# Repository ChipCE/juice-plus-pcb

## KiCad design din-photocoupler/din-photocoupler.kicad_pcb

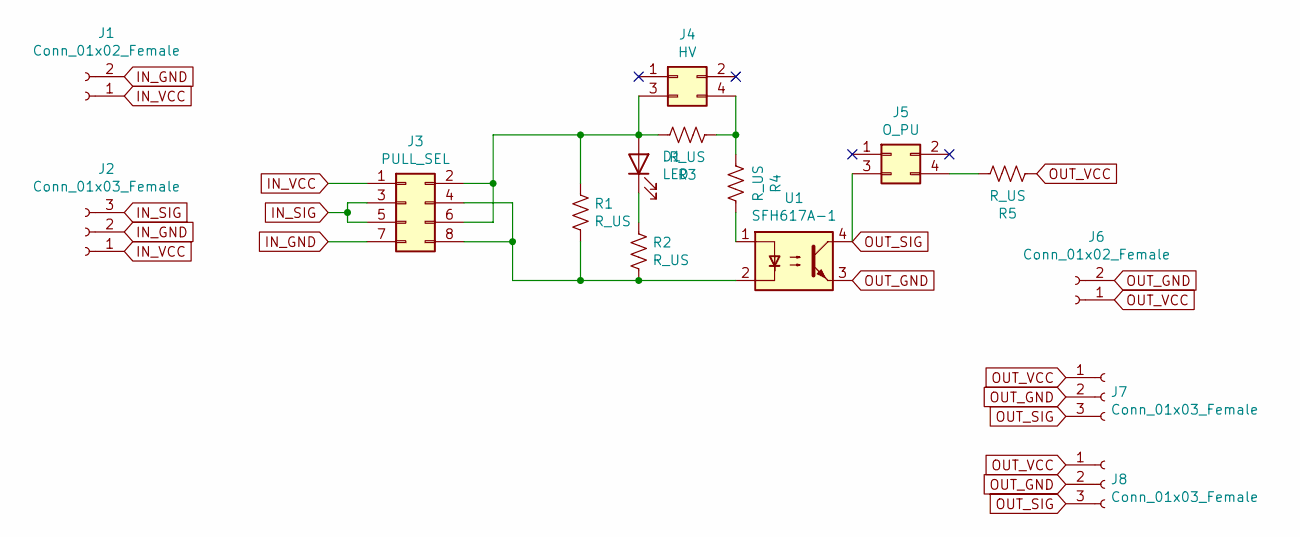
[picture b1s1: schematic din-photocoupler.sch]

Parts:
D1: LED; LED_0805_2012Metric_Pad1.15x1.40mm_HandSolder
J1, J6: Conn_01x02_Female; JST_XH_B2B-XH-A_1x02_P2.50mm_Vertical
J2, J7, J8: Conn_01x03_Female; JST_XH_B3B-XH-A_1x03_P2.50mm_Vertical
J3: PULL_SEL; PinHeader_2x04_P2.54mm_Vertical
J4: HV; PinHeader_2x02_P2.54mm_Vertical
J5: O_PU; PinHeader_2x02_P2.54mm_Vertical
R1, R2, R3, R4, R5: R_US; R_0805_2012Metric_Pad1.20x1.40mm_HandSolder
U1: SFH617A-1; DIP-4_W7.62mm

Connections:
IN_GND: J1.2, J2.2, J3.7
IN_SIG: J2.3, J3.3, J3.5
IN_VCC: J1.1, J2.1, J3.1
unnamed: D1.1 (K), R2.2
unnamed: D1.2 (A), J3.2, J3.6, J4.3, R1.2, R3.1
unnamed: J3.4, J3.8, R1.1, R2.1, U1.2
unnamed: J4.4, R3.2, R4.2
unnamed: J5.4, R5.1
unnamed: R4.1, U1.1
OUT_GND: J6.2, J7.2, J8.2, U1.3
OUT_SIG: J5.3, J7.3, J8.3, U1.4
OUT_VCC: J6.1, J7.1, J8.1, R5.2

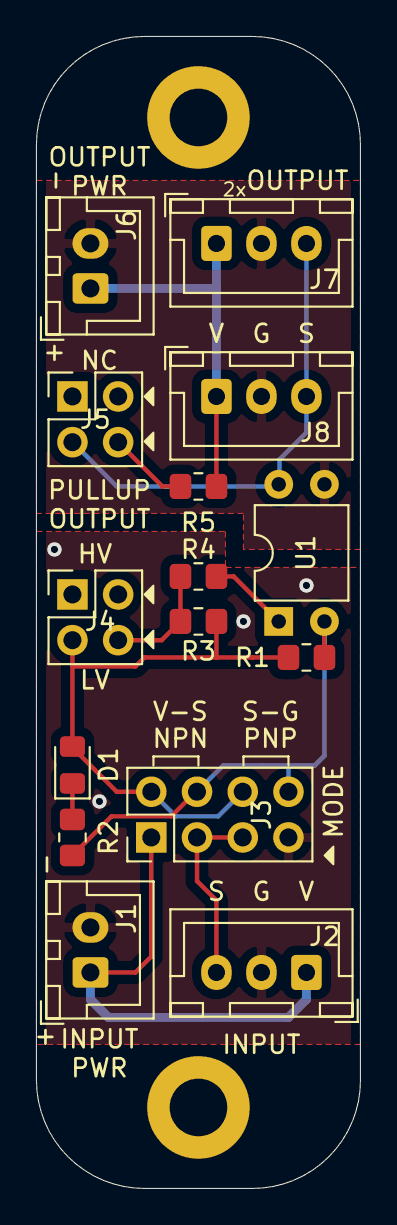
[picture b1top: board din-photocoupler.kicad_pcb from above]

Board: 2 copper layers, 18.0 x 64.0 mm, 15 parts (0 on the bottom side), 12 nets.

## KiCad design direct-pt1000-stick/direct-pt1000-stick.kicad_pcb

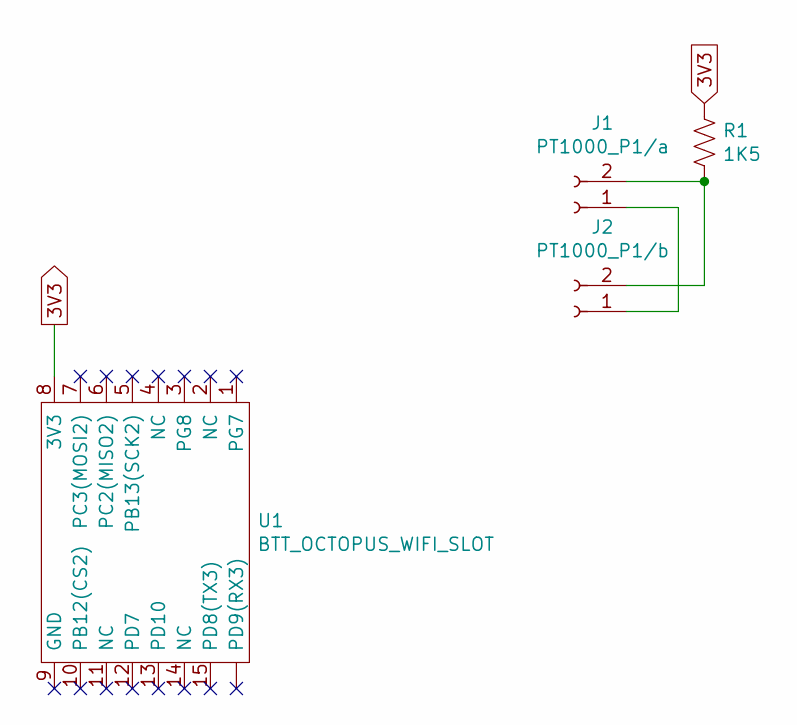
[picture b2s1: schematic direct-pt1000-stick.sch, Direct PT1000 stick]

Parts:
J1: PT1000_P1/a; JST_XH_S2B-XH-A-1_1x02_P2.50mm_Horizontal
J2: PT1000_P1/b; JST_XH_S2B-XH-A-1_1x02_P2.50mm_Horizontal
R1: 1K5; R_0805_2012Metric_Pad1.20x1.40mm_HandSolder
U1: BTT_OCTOPUS_WIFI_SLOT

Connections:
3V3: R1.1, U1.8 (3V3)
unnamed: J1.1, J2.1
unnamed: J1.2, J2.2, R1.2

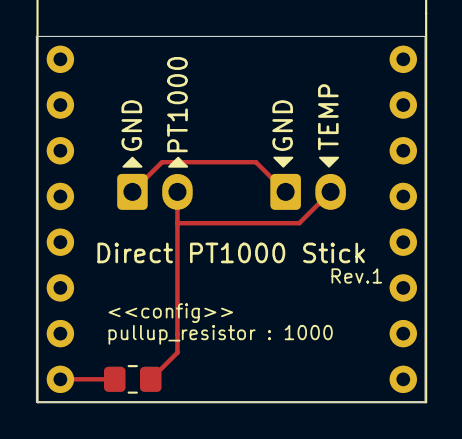
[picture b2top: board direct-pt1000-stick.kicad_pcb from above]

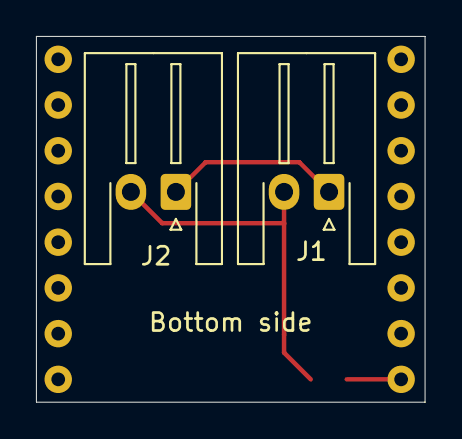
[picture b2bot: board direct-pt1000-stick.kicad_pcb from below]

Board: 2 copper layers, 21.6 x 20.3 mm, 4 parts (2 on the bottom side), 3 nets.

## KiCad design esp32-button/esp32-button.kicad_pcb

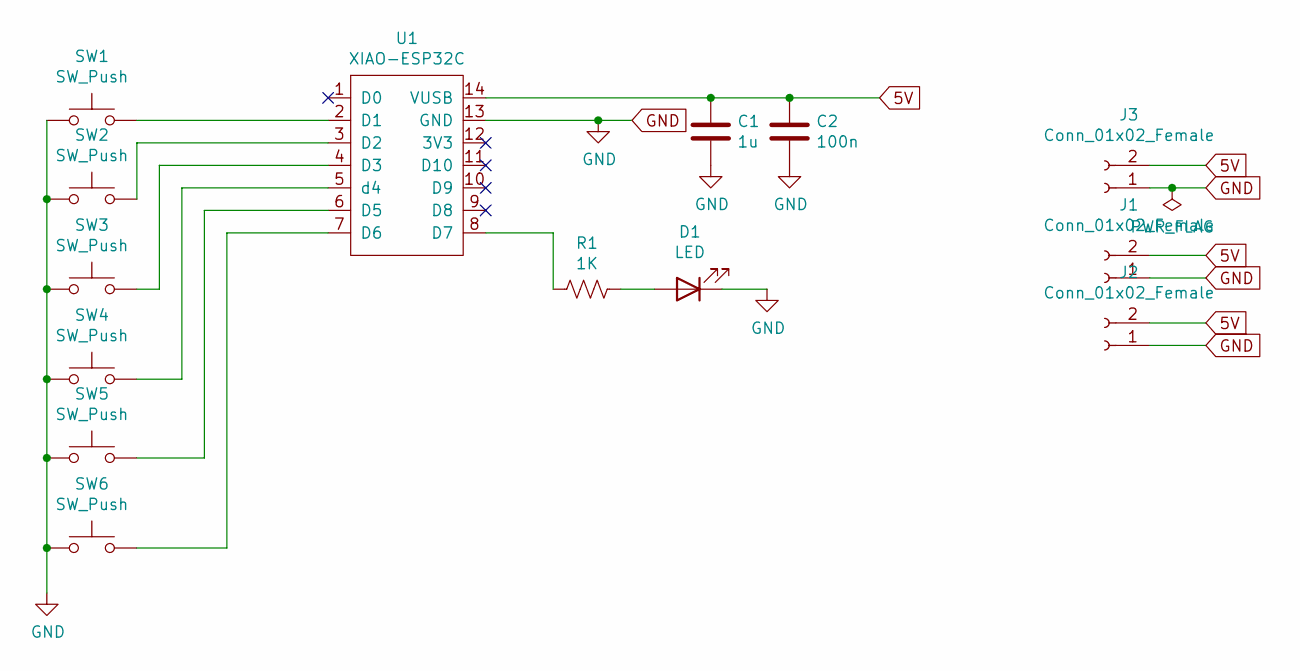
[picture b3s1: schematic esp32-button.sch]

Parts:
C1: 1u; C_0805_2012Metric_Pad1.18x1.45mm_HandSolder
C2: 100n; C_0805_2012Metric_Pad1.18x1.45mm_HandSolder
D1: LED; LED_0805_2012Metric_Pad1.15x1.40mm_HandSolder
J1, J2, J3: Conn_01x02_Female; solder-pad-2p
R1: 1K; R_0805_2012Metric_Pad1.20x1.40mm_HandSolder
SW1, SW2, SW3, SW4, SW5, SW6: SW_Push; SW_Push_1P1T_NO_6x6mm_H9.5mm
U1: XIAO-ESP32C; XIAO_ESP32C_SMD

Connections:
5V: C1.1, C2.1, J1.2, J2.2, J3.2, U1.14 (VUSB)
GND: C1.2, C2.2, D1.1 (K), J1.1, J2.1, J3.1, SW1.1, SW2.1, SW3.1, SW4.1, SW5.1, SW6.1, U1.13 (GND)
unnamed: D1.2 (A), R1.1
unnamed: R1.2, U1.8 (D7)
unnamed: SW1.2, U1.2 (D1)
unnamed: SW2.2, U1.3 (D2)
unnamed: SW3.2, U1.4 (D3)
unnamed: SW4.2, U1.5 (d4)
unnamed: SW5.2, U1.6 (D5)
unnamed: SW6.2, U1.7 (D6)

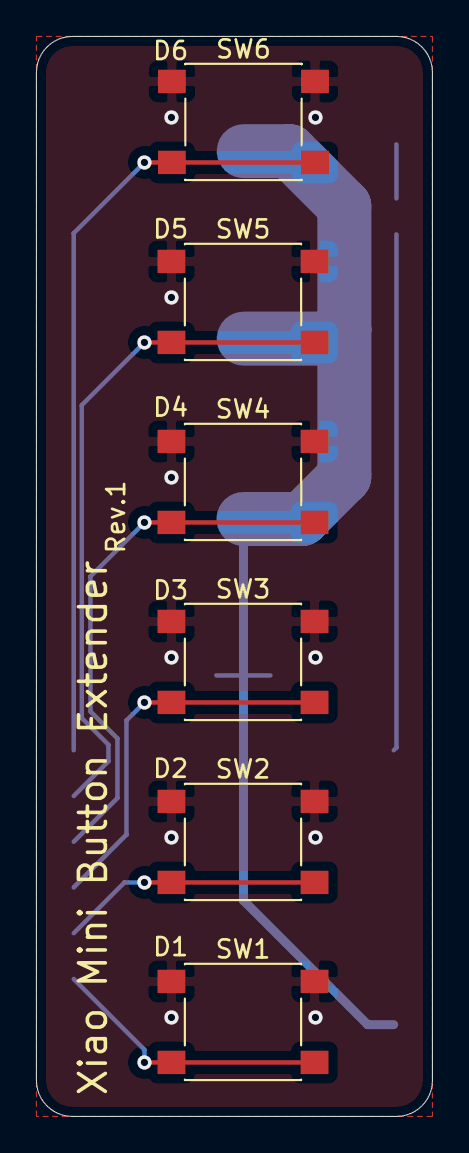
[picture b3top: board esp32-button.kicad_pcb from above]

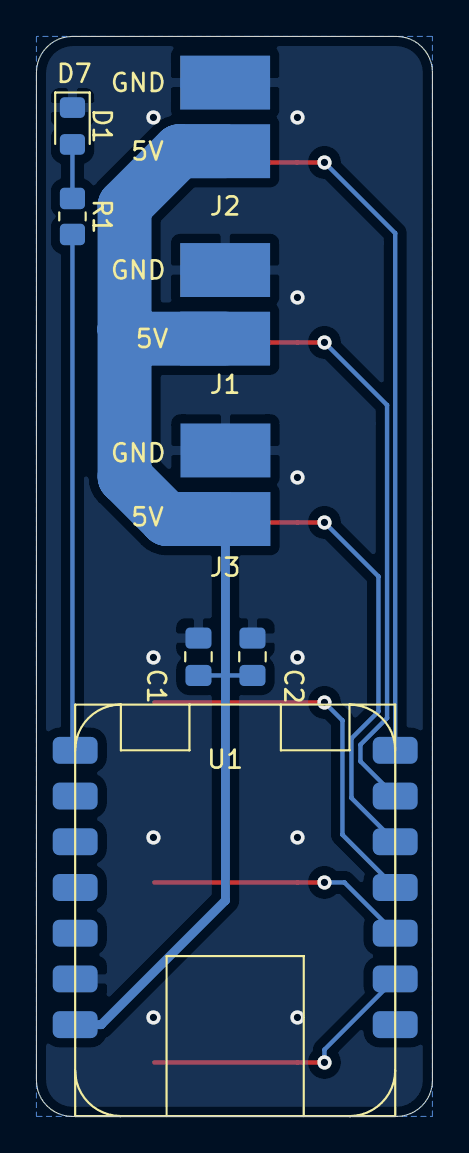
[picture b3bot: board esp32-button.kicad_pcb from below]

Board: 2 copper layers, 22.0 x 60.0 mm, 14 parts (8 on the bottom side), 10 nets.

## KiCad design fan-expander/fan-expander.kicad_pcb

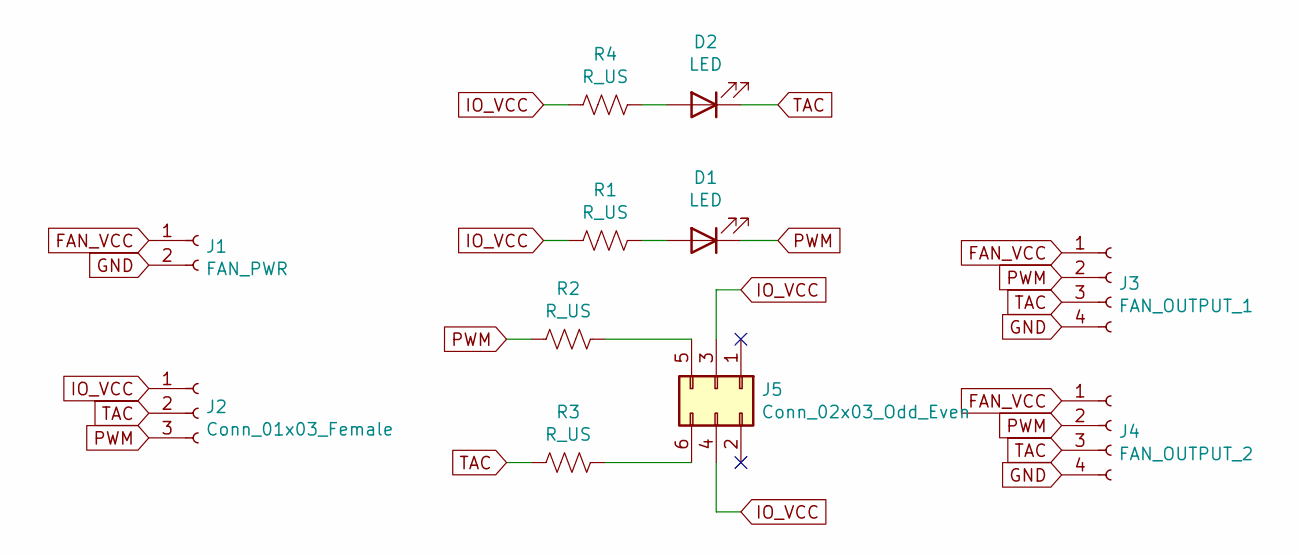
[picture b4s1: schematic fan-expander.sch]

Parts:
D1, D2: LED; LED_0805_2012Metric_Pad1.15x1.40mm_HandSolder
J1: FAN_PWR; JST_XH_B2B-XH-A_1x02_P2.50mm_Vertical
J2: Conn_01x03_Female; JST_XH_B3B-XH-A_1x03_P2.50mm_Vertical
J3: FAN_OUTPUT_1; JST_XH_B4B-XH-A_1x04_P2.50mm_Vertical
J4: FAN_OUTPUT_2; JST_XH_B4B-XH-A_1x04_P2.50mm_Vertical
J5: Conn_02x03_Odd_Even; PinHeader_2x03_P2.54mm_Vertical
R1, R2, R3, R4: R_US; R_0805_2012Metric_Pad1.20x1.40mm_HandSolder

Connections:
FAN_VCC: J1.1, J3.1, J4.1
GND: J1.2, J3.4, J4.4
IO_VCC: J2.1, J5.3, J5.4, R1.2, R4.2
unnamed: D1.2 (A), R1.1
unnamed: D2.2 (A), R4.1
unnamed: J5.5, R2.1
unnamed: J5.6, R3.1
PWM: D1.1 (K), J2.3, J3.2, J4.2, R2.2
TAC: D2.1 (K), J2.2, J3.3, J4.3, R3.2

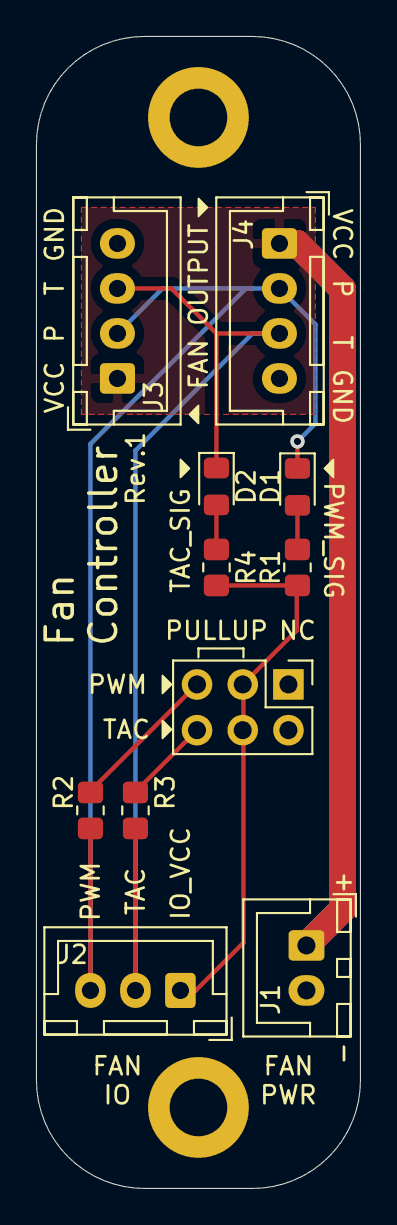
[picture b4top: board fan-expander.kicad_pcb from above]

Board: 2 copper layers, 18.0 x 64.0 mm, 11 parts (0 on the bottom side), 9 nets.

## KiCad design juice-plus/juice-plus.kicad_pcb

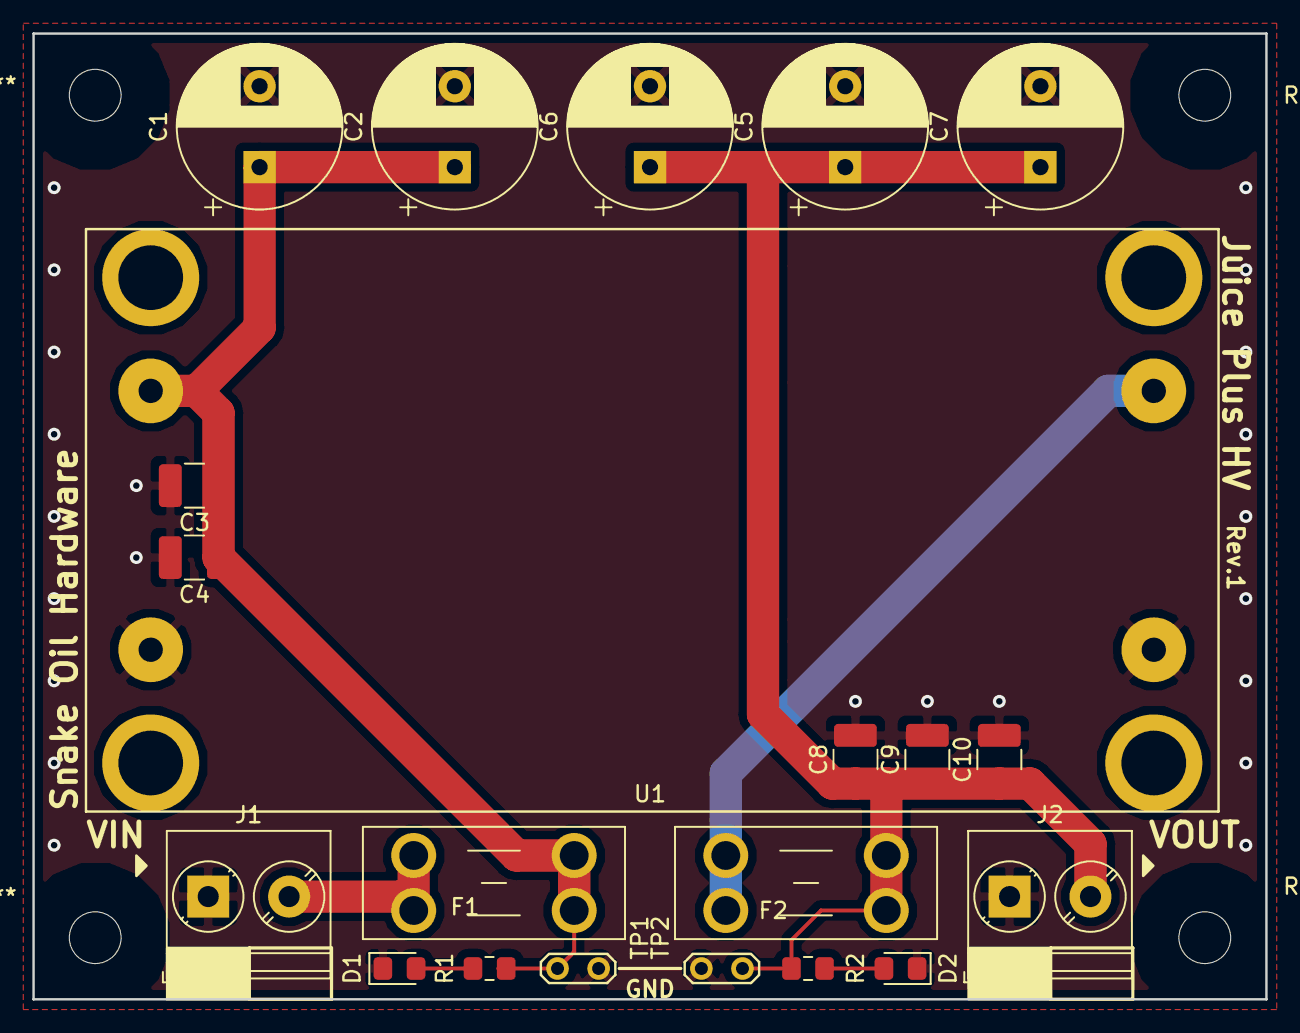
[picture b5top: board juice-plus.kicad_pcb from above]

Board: 2 copper layers, 76.2 x 59.7 mm, 21 parts (0 on the bottom side), 7 nets.

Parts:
C1, C2: 470u; CP_Radial_D10.0mm_P5.00mm
C3, C4, C8, C9, C10: 100n; C_1210_3225Metric_Pad1.42x2.65mm_HandSolder
C5, C6, C7: 330u; CP_Radial_D10.0mm_P5.00mm
D1: PWR_24; LED_0805_2012Metric_Pad1.15x1.40mm_HandSolder
D2: PWR_HV; LED_0805_2012Metric_Pad1.15x1.40mm_HandSolder
F1: VIN_Fuse; Fuseholder_Blade_Mini_Keystone_3568
F2: HV_Fuse; Fuseholder_Blade_Mini_Keystone_3568
J1: V_IN; TerminalBlock_Phoenix_PT-1,5-2-5.0-H_1x02_P5.00mm_Horizontal
J2: HV_OUT; TerminalBlock_Phoenix_PT-1,5-2-5.0-H_1x02_P5.00mm_Horizontal
R1: 6K8; R_0805_2012Metric_Pad1.15x1.40mm_HandSolder
R2: 10K; R_0805_2012Metric_Pad1.15x1.40mm_HandSolder
TP1: VIN_TP; TestPoint_2Pads_Pitch2.54mm_Drill0.8mm
TP2: HV_TP; TestPoint_2Pads_Pitch2.54mm_Drill0.8mm
U1: Boost-converter-9-48V; boost-converter-9-48V

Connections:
+24V: C1.1, C2.1, C3.1, C4.1, F1.1, R1.1, TP1.2, U1.2
GND: C1.2, C2.2, C3.2, C4.2, C5.2, C6.2, C7.2, C8.2, C9.2, C10.2, D1.1, D2.1, J1.1, J2.1, TP1.1, TP2.1, U1.1, U1.3
unnamed: C5.1, C6.1, C7.1, C8.1, C9.1, C10.1, F2.1, J2.2, R2.1, TP2.2
unnamed: D1.2, R1.2
unnamed: D2.2, R2.2
unnamed: F1.2, J1.2
unnamed: F2.2, U1.4

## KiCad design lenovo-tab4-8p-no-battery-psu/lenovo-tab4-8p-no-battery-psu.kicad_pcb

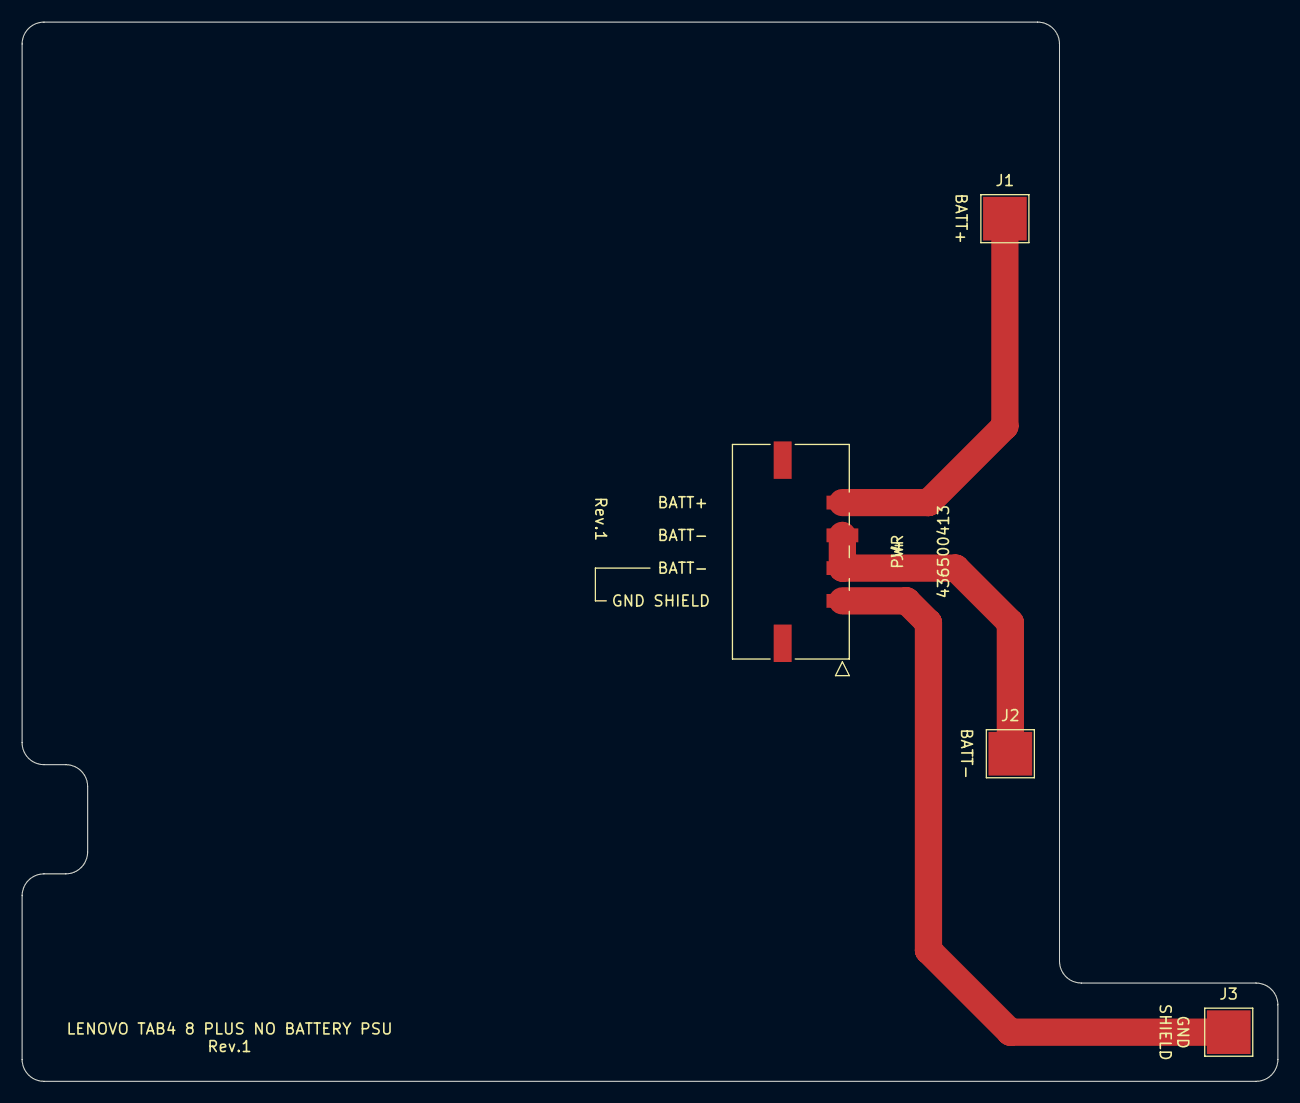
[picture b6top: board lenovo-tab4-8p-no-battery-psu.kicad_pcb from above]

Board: 2 copper layers, 115.0 x 97.0 mm, 4 parts (0 on the bottom side), 3 nets.

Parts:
J1: BATT+; TestPoint_Pad_4.0x4.0mm
J2: BATT-; TestPoint_Pad_4.0x4.0mm
J3: GND_SHIELD; TestPoint_Pad_4.0x4.0mm
J4: PWR; molex_1x4_smd

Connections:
BATT+: J1.1, J4.4
BATT-: J2.1, J4.2, J4.3
GND_SHIELD: J3.1, J4.1

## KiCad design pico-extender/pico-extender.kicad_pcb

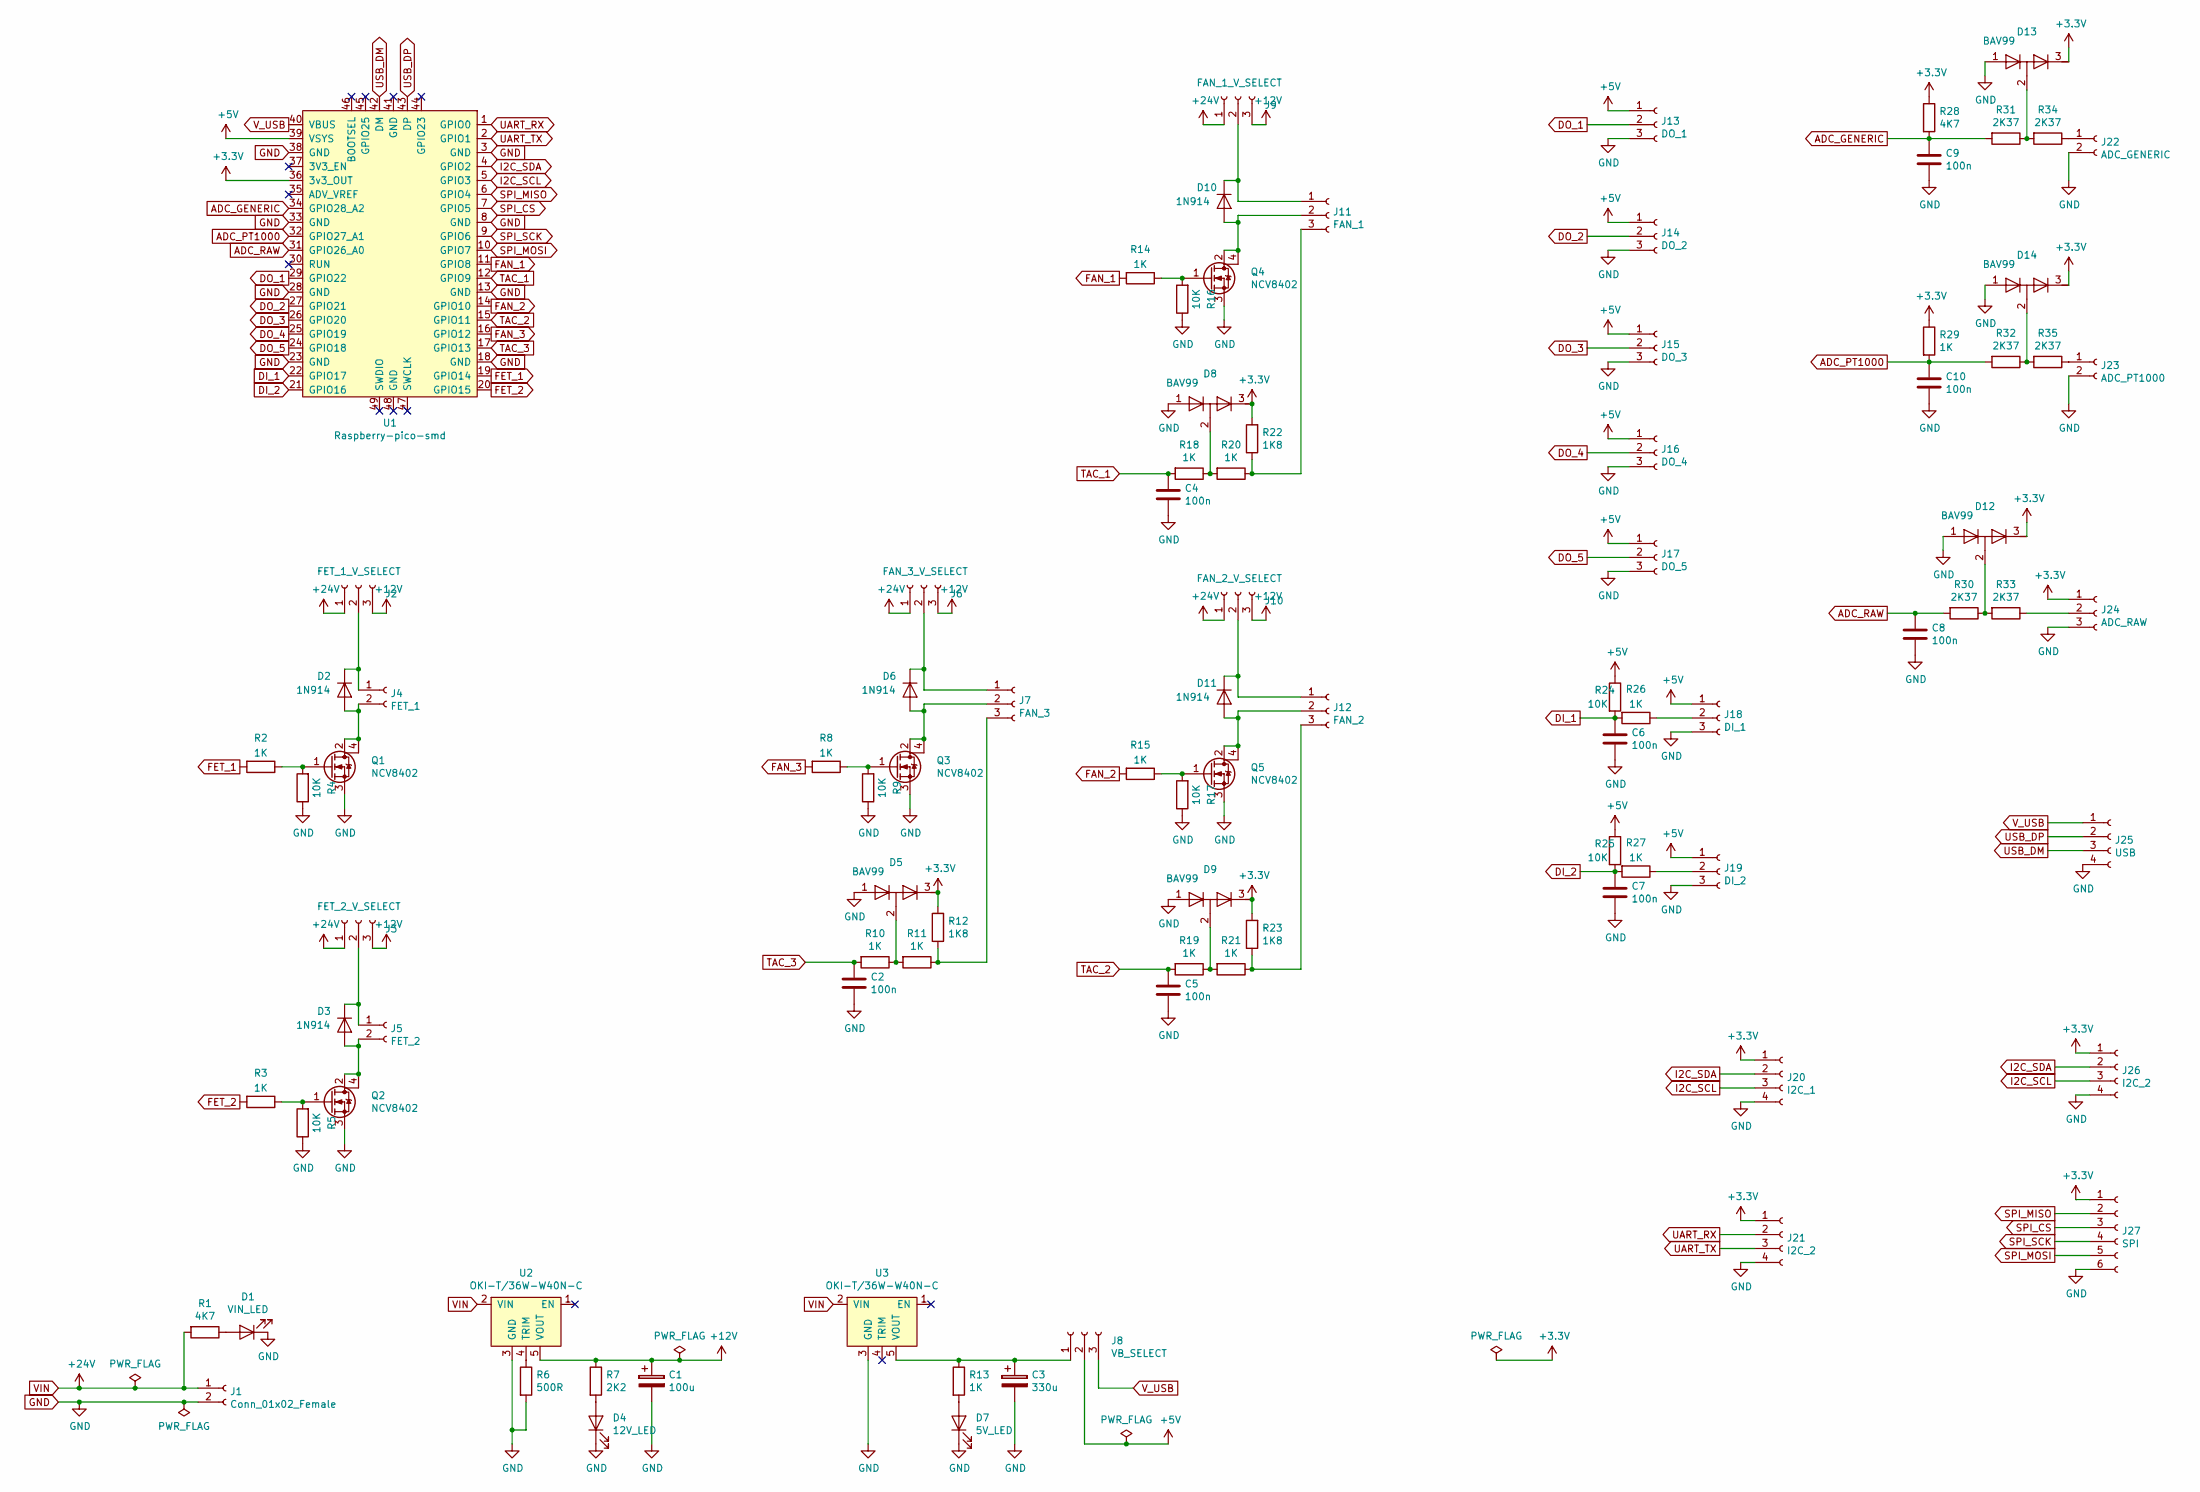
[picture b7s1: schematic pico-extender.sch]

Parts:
C1: 100u; CP_Elec_10x10
C2, C4, C5, C6, C7, C8, C9, C10: 100n; C_0603_1608Metric
C3: 330u; CP_Elec_10x10
D1: VIN_LED; LED_0805_2012Metric
D2, D3, D6, D10, D11: 1N914; D_SOD-523
D4: 12V_LED; LED_0805_2012Metric
D5, D8, D9, D12, D13, D14: BAV99; SOT-323_SC-70
D7: 5V_LED; LED_0805_2012Metric
J1: Conn_01x02_Female; TerminalBlock_Phoenix_PT-1,5-2-5.0-H_1x02_P5.00mm_Horizontal
J2: FET_1_V_SELECT; PinHeader_1x03_P2.54mm_Vertical
J3: FET_2_V_SELECT; PinHeader_1x03_P2.54mm_Vertical
J4: FET_1; JST_XH_B02B-XH-A_1x02_P2.50mm_Vertical
J5: FET_2; JST_XH_B02B-XH-A_1x02_P2.50mm_Vertical
J6: FAN_3_V_SELECT; PinHeader_1x03_P2.54mm_Vertical
J7: FAN_3; JST_XH_B03B-XH-A_1x03_P2.50mm_Vertical
J8: VB_SELECT; PinHeader_1x03_P2.54mm_Vertical
J9: FAN_1_V_SELECT; PinHeader_1x03_P2.54mm_Vertical
J10: FAN_2_V_SELECT; PinHeader_1x03_P2.54mm_Vertical
J11: FAN_1; JST_XH_B03B-XH-A_1x03_P2.50mm_Vertical
J12: FAN_2; JST_XH_B03B-XH-A_1x03_P2.50mm_Vertical
J13: DO_1; JST_XH_B03B-XH-A_1x03_P2.50mm_Vertical
J14: DO_2; JST_XH_B03B-XH-A_1x03_P2.50mm_Vertical
J15: DO_3; JST_XH_B03B-XH-A_1x03_P2.50mm_Vertical
J16: DO_4; JST_XH_B03B-XH-A_1x03_P2.50mm_Vertical
J17: DO_5; JST_XH_B03B-XH-A_1x03_P2.50mm_Vertical
J18: DI_1; JST_XH_B03B-XH-A_1x03_P2.50mm_Vertical
J19: DI_2; JST_XH_B03B-XH-A_1x03_P2.50mm_Vertical
J20: I2C_1; JST_XH_B04B-XH-A_1x04_P2.50mm_Vertical
J21, J26: I2C_2; JST_XH_B04B-XH-A_1x04_P2.50mm_Vertical
J22: ADC_GENERIC; JST_XH_B02B-XH-A_1x02_P2.50mm_Vertical
J23: ADC_PT1000; JST_XH_B02B-XH-A_1x02_P2.50mm_Vertical
J24: ADC_RAW; JST_XH_B03B-XH-A_1x03_P2.50mm_Vertical
J25: USB; JST_XH_B04B-XH-A_1x04_P2.50mm_Vertical
J27: SPI; JST_XH_B06B-XH-A_1x06_P2.50mm_Vertical
Q1, Q2, Q3, Q4, Q5: NCV8402; SOT-223
R1, R28: 4K7; R_0603_1608Metric
R2, R3, R8, R10, R11, R13, R14, R15, R18, R19, R20, R21, R26, R27, R29: 1K; R_0603_1608Metric
R4, R5, R9, R16, R17, R24, R25: 10K; R_0603_1608Metric
R6: 500R; R_0603_1608Metric
R7: 2K2; R_0603_1608Metric
R12, R22, R23: 1K8; R_0603_1608Metric
R30, R31, R32, R33, R34, R35: 2K37; R_0603_1608Metric
U1: Raspberry-pico-smd
U2, U3: OKI-T/36W-W40N-C; OKI-T-DOSA-th

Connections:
+3V3: D5.3 (K), D8.3 (K), D9.3 (K), D12.3 (K), D13.3 (K), D14.3 (K), J20.1, J21.1, J24.1, J26.1, J27.1, R12.2, R22.2, R23.2, R28.1, R29.1, U1.36 (3v3_OUT)
+5V: J8.2, J13.1, J14.1, J15.1, J16.1, J17.1, J18.1, J19.1, R24.1, R25.1, U1.39 (VSYS)
+12V: C1.1, J2.3, J3.3, J6.3, J9.3, J10.3, R7.1, U2.5 (VOUT)
ADC_GENERIC: C9.1, R28.2, R31.2, U1.34 (GPIO28_A2)
ADC_PT1000: C10.1, R29.2, R32.2, U1.32 (GPIO27_A1)
ADC_RAW: C8.1, R30.2, U1.31 (GPIO26_A0)
DI_1: C6.1, R24.2, R26.2, U1.22 (GPIO17)
DI_2: C7.1, R25.2, R27.2, U1.21 (GPIO16)
DO_1: J13.2, U1.29 (GPIO22)
DO_2: J14.2, U1.27 (GPIO21)
DO_3: J15.2, U1.26 (GPIO20)
DO_4: J16.2, U1.25 (GPIO19)
DO_5: J17.2, U1.24 (GPIO18)
FAN_1: R14.2, U1.11 (GPIO8)
FAN_2: R15.2, U1.14 (GPIO10)
FAN_3: R8.2, U1.16 (GPIO12)
FET_1: R2.2, U1.19 (GPIO14)
FET_2: R3.2, U1.20 (GPIO15)
GND: C1.2, C2.2, C3.2, C4.2, C5.2, C6.2, C7.2, C8.2, C9.2, C10.2, D1.1 (K), D4.1 (K), D5.1 (A), D7.1 (K), D8.1 (A), D9.1 (A), D12.1 (A), D13.1 (A), D14.1 (A), J1.2, J13.3, J14.3, J15.3, J16.3, J17.3, J18.3, J19.3, J20.4, J21.4, J22.2, J23.2, J24.3, J25.4, J26.4, J27.6, Q1.3 (S), Q2.3 (S), Q3.3 (S), Q4.3 (S), Q5.3 (S), R4.1, R5.1, R6.2, R9.1, R16.1, R17.1, U1.3 (GND), U1.8 (GND), U1.13 (GND), U1.18 (GND), U1.23 (GND), U1.28 (GND), U1.33 (GND), U1.38 (GND), U2.3 (GND), U3.3 (GND)
I2C_SCL: J20.3, J26.3, U1.5 (GPIO3)
I2C_SDA: J20.2, J26.2, U1.4 (GPIO2)
unnamed: C3.1, J8.1, R13.1, U3.5 (VOUT)
unnamed: D1.2 (A), R1.1
unnamed: D2.1 (K), J2.2, J4.1
unnamed: D2.2 (A), J4.2, Q1.2 (D), Q1.4 (D)
unnamed: D3.1 (K), J3.2, J5.1
unnamed: D3.2 (A), J5.2, Q2.2 (D), Q2.4 (D)
unnamed: D4.2 (A), R7.2
unnamed: D5.2 (common), R10.1, R11.2
unnamed: D6.1 (K), J6.2, J7.1
unnamed: D6.2 (A), J7.2, Q3.2 (D), Q3.4 (D)
unnamed: D7.2 (A), R13.2
unnamed: D8.2 (common), R18.1, R20.2
unnamed: D9.2 (common), R19.1, R21.2
unnamed: D10.1 (K), J9.2, J11.1
unnamed: D10.2 (A), J11.2, Q4.2 (D), Q4.4 (D)
unnamed: D11.1 (K), J10.2, J12.1
unnamed: D11.2 (A), J12.2, Q5.2 (D), Q5.4 (D)
unnamed: D12.2 (common), R30.1, R33.2
unnamed: D13.2 (common), R31.1, R34.2
unnamed: D14.2 (common), R32.1, R35.2
unnamed: J7.3, R11.1, R12.1
unnamed: J11.3, R20.1, R22.1
unnamed: J12.3, R21.1, R23.1
unnamed: J18.2, R26.1
unnamed: J19.2, R27.1
unnamed: J22.1, R34.1
unnamed: J23.1, R35.1
unnamed: J24.2, R33.1
unnamed: Q1.1 (G), R2.1, R4.2
unnamed: Q2.1 (G), R3.1, R5.2
unnamed: Q3.1 (G), R8.1, R9.2
unnamed: Q4.1 (G), R14.1, R16.2
unnamed: Q5.1 (G), R15.1, R17.2
unnamed: R6.1, U2.4 (TRIM)
SPI_CS: J27.3, U1.7 (GPIO5)
SPI_MISO: J27.2, U1.6 (GPIO4)
SPI_MOSI: J27.5, U1.10 (GPIO7)
SPI_SCK: J27.4, U1.9 (GPIO6)
TAC_1: C4.1, R18.2, U1.12 (GPIO9)
TAC_2: C5.1, R19.2, U1.15 (GPIO11)
TAC_3: C2.1, R10.2, U1.17 (GPIO13)
UART_RX: J21.2, U1.1 (GPIO0)
UART_TX: J21.3, U1.2 (GPIO1)
USB_DM: J25.3, U1.42 (DM)
USB_DP: J25.2, U1.43 (DP)
VIN: J1.1, J2.1, J3.1, J6.1, J9.1, J10.1, R1.2, U2.2 (VIN), U3.2 (VIN)
V_USB: J8.3, J25.1, U1.40 (VBUS)

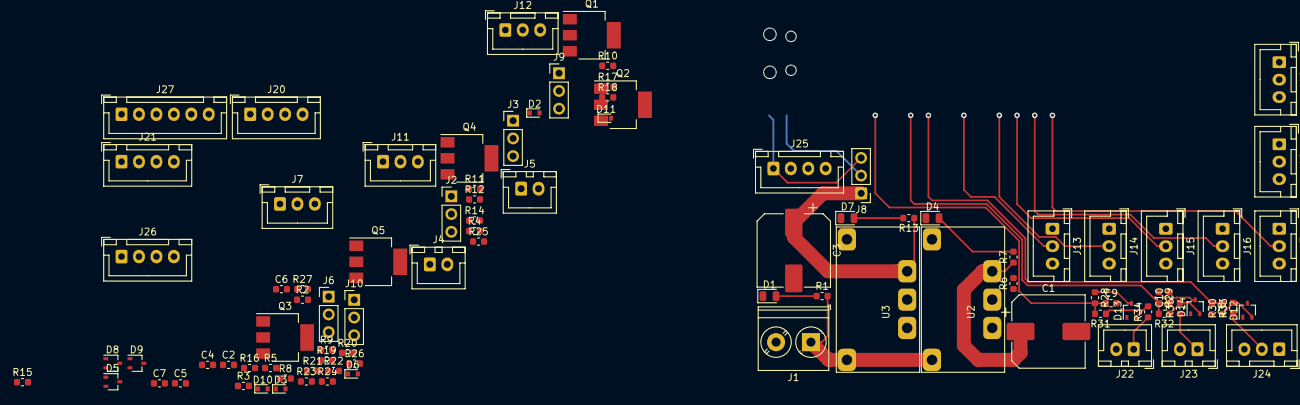
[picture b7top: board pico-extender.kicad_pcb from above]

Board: 4 copper layers, 94 parts (1 on the bottom side), 68 nets.

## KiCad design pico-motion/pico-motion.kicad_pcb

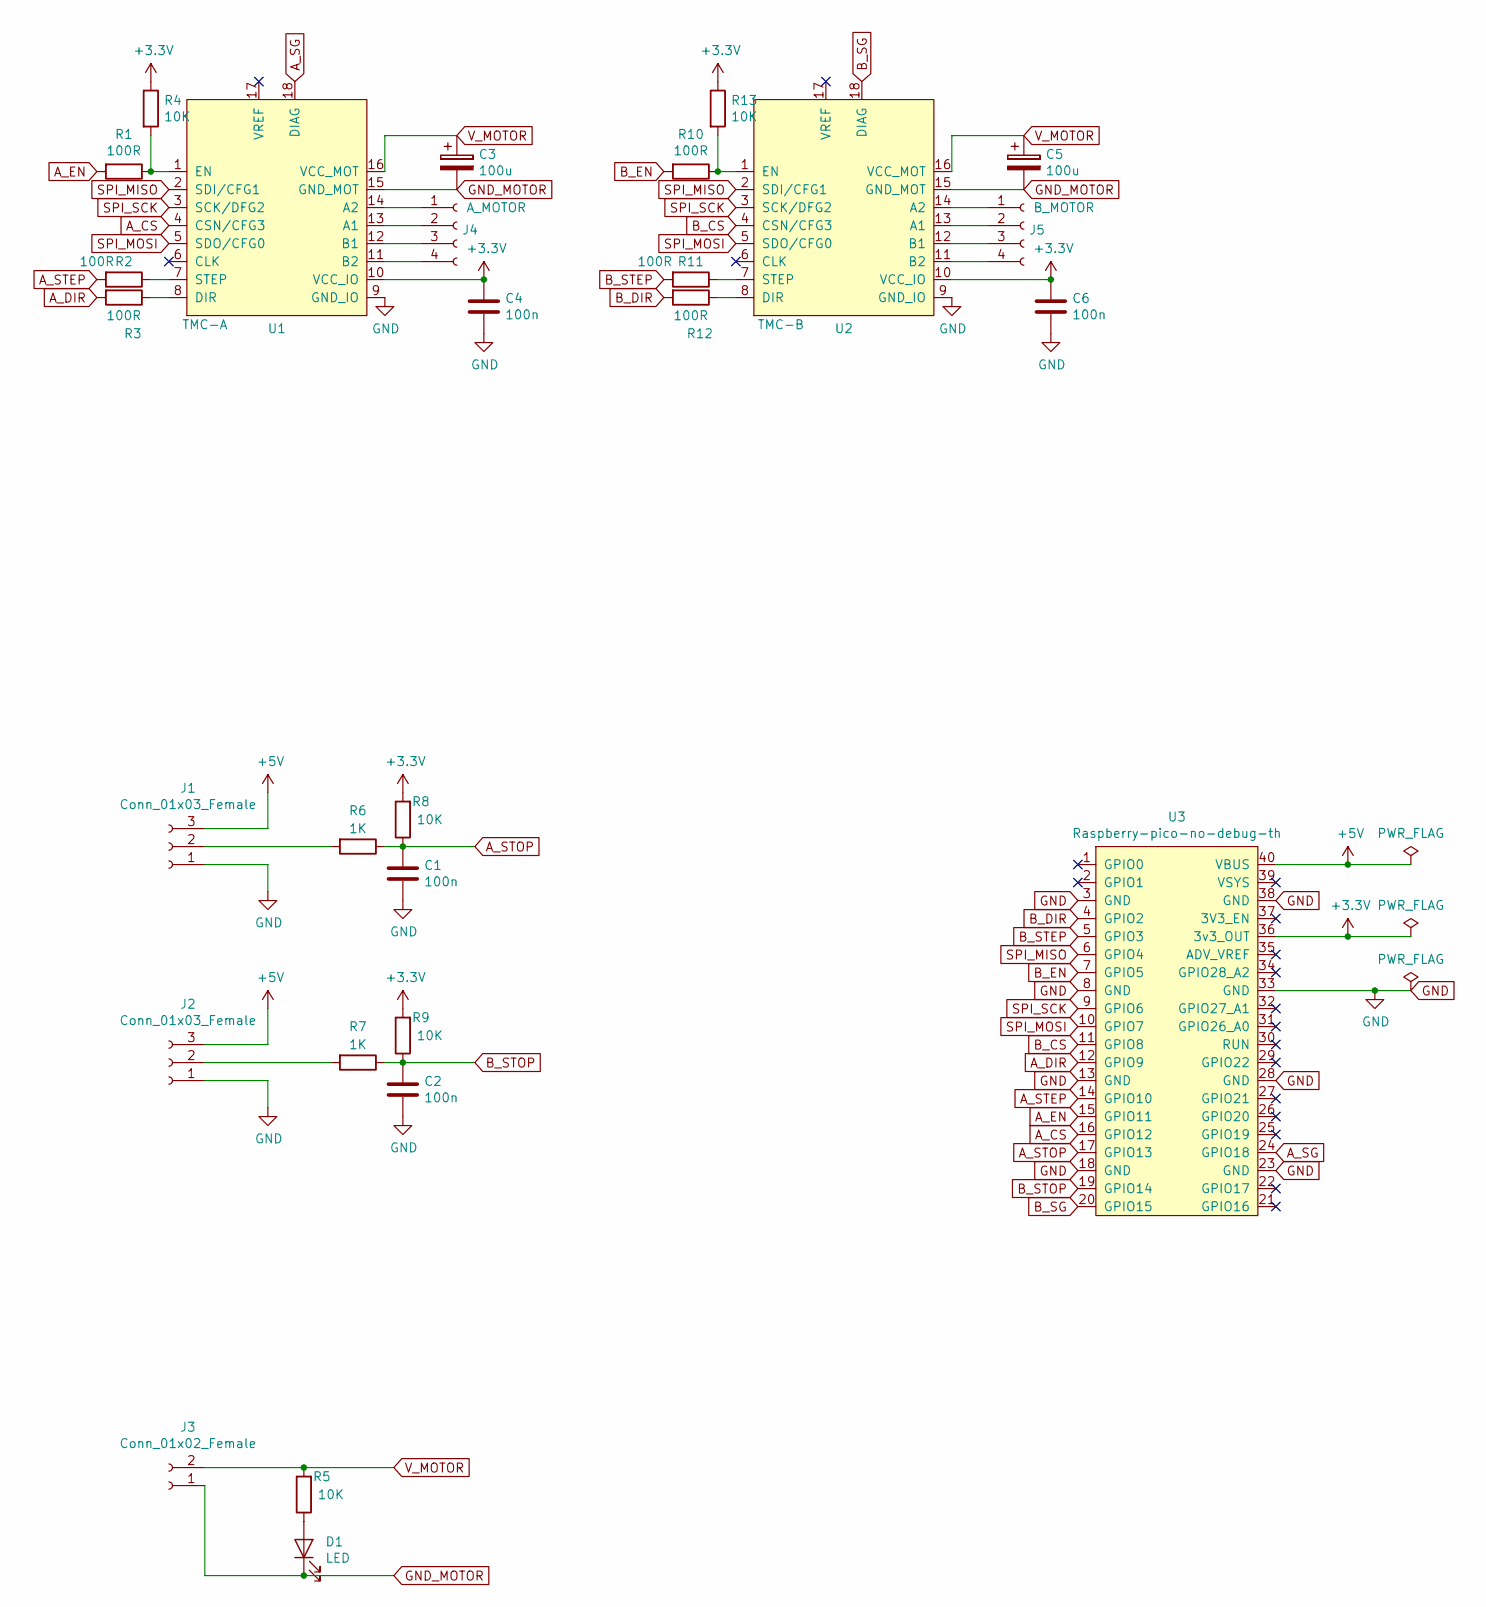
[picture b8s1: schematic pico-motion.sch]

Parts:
C1, C2, C4, C6: 100n; C_0603_1608Metric
C3, C5: 100u; CP_Elec_10x10.5
D1: LED; LED_0805_2012Metric
J1, J2: Conn_01x03_Female; JST_XH_B03B-XH-A_1x03_P2.50mm_Vertical
J3: Conn_01x02_Female; JST_XH_B02B-XH-A_1x02_P2.50mm_Vertical
J4: A_MOTOR; JST_XH_B04B-XH-A_1x04_P2.50mm_Vertical
J5: B_MOTOR; JST_XH_B04B-XH-A_1x04_P2.50mm_Vertical
R1, R2, R3, R10, R11, R12: 100R; R_0603_1608Metric
R4, R8, R9, R13: 10K; R_0603_1608Metric
R5: 10K; R_0805_2012Metric
R6, R7: 1K; R_0603_1608Metric
U1: TMC-A; TMC-step-stick
U2: TMC-B; TMC-step-stick
U3: Raspberry-pico-no-debug-th; raspberry_pico_under

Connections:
+3V3: C4.1, C6.1, R4.1, R8.2, R9.2, R13.1, U1.10 (VCC_IO), U2.10 (VCC_IO), U3.36 (3v3_OUT)
+5V: J1.3, J2.3, U3.40 (VBUS)
A_CS: U1.4 (CSN/CFG3), U3.16 (GPIO12)
A_DIR: R3.2, U3.12 (GPIO9)
A_EN: R1.2, U3.15 (GPIO11)
A_SG: U1.18 (DIAG), U3.24 (GPIO18)
A_STEP: R2.2, U3.14 (GPIO10)
A_STOP: C1.1, R6.1, R8.1, U3.17 (GPIO13)
B_CS: U2.4 (CSN/CFG3), U3.11 (GPIO8)
B_DIR: R12.2, U3.4 (GPIO2)
B_EN: R10.2, U3.7 (GPIO5)
B_SG: U2.18 (DIAG), U3.20 (GPIO15)
B_STEP: R11.2, U3.5 (GPIO3)
B_STOP: C2.1, R7.1, R9.1, U3.19 (GPIO14)
GND: C1.2, C2.2, C4.2, C6.2, J1.1, J2.1, U1.9 (GND_IO), U2.9 (GND_IO), U3.3 (GND), U3.8 (GND), U3.13 (GND), U3.18 (GND), U3.23 (GND), U3.28 (GND), U3.33 (GND), U3.38 (GND)
GND_MOTOR: C3.2, C5.2, D1.1 (K), J3.1, U1.15 (GND_MOT), U2.15 (GND_MOT)
unnamed: D1.2 (A), R5.1
unnamed: J1.2, R6.2
unnamed: J2.2, R7.2
unnamed: J4.1, U1.14 (A2)
unnamed: J4.2, U1.13 (A1)
unnamed: J4.3, U1.12 (B1)
unnamed: J4.4, U1.11 (B2)
unnamed: J5.1, U2.14 (A2)
unnamed: J5.2, U2.13 (A1)
unnamed: J5.3, U2.12 (B1)
unnamed: J5.4, U2.11 (B2)
unnamed: R1.1, R4.2, U1.1 (EN)
unnamed: R2.1, U1.7 (STEP)
unnamed: R3.1, U1.8 (DIR)
unnamed: R10.1, R13.2, U2.1 (EN)
unnamed: R11.1, U2.7 (STEP)
unnamed: R12.1, U2.8 (DIR)
SPI_MISO: U1.2 (SDI/CFG1), U2.2 (SDI/CFG1), U3.6 (GPIO4)
SPI_MOSI: U1.5 (SDO/CFG0), U2.5 (SDO/CFG0), U3.10 (GPIO7)
SPI_SCK: U1.3 (SCK/DFG2), U2.3 (SCK/DFG2), U3.9 (GPIO6)
V_MOTOR: C3.1, C5.1, J3.2, R5.2, U1.16 (VCC_MOT), U2.16 (VCC_MOT)

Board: 4 copper layers, 28 parts (0 on the bottom side), 37 nets, no tracks yet.

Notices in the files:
parts and their libraries:
Copyright 2021 Accelerated Designs. All rights reserved.
